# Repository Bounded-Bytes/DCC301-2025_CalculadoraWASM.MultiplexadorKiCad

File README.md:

# Repositório de Atividades Extras – AOC

### Autor: Gabriel Guilherme Figueiredo (2024005507)

Este repositório contém duas atividades extras para a disciplina de **AOC**:

1. **Calculadora WebAssembly**  
2. **Multiplexador 4x1 – KiCad e PCB**

---

## 1️⃣ Calculadora WebAssembly

- **Descrição:** Projeto de uma calculadora aritmética simples implementada em C, compilada para WebAssembly usando Emscripten, com interface HTML/JS.  
- **Ferramentas usadas:** C, Emscripten, HTML, JavaScript.  
- **Conteúdo da pasta `CalculadoraWASM`:**  
  - `index.html` → interface da calculadora  
  - `calculadora.c` → código C da calculadora  
  - `calculadora.js` e `calculadora.wasm` → arquivos gerados pelo Emscripten 

- **Como testar:**
  1. Fazer download da pasta `CalculadoraWASM`
  2. Rodar um servidor HTTP local (`python -m http.server 8000`)
  3. Abrir `http://localhost:8000` no navegador

---

## 2️⃣ Multiplexador 4x1 – KiCad

- **Descrição:** Projeto de um multiplexador 4x1, com esquemático completo e PCB pronta para fabricação.  
- **Ferramentas usadas:** KiCad.
- **Conteúdo da pasta `MultiplexadorKiCad`:**
  - `multiplexador.kicad_sch` → esquemático elétrico do circuito
  - `multiplexador.kicad_pcb` → layout da placa PCB
  - `imagem-esquematico.png`, `imagem-PCB-topo.png`, e `imagem-PCB-fundo.png` → imagens do diagrama e PCB do circuito

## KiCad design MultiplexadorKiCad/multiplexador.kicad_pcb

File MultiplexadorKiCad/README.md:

# Multiplexador 4x1

Este documento descreve o projeto de um **Multiplexador 4x1** implementado com **CIs da série 74LSxx**, incluindo o **esquemático elétrico** e a **estimativa de custo de fabricação da PCB** (Placa de Circuito Impresso).

---

## 1. Descrição do Circuito

O circuito implementa a lógica booleana de um **Multiplexador 4x1**, que seleciona uma entre quatro entradas de dados (`E0`, `E1`, `E2`, `E3`) e a encaminha para uma única saída (`OUT_final`), de acordo com a combinação de dois bits seletores (`S1`, `S0`).

### **Função lógica do circuito:** $$OUT_{\text{final}} = (E_0 \cdot \overline{S_1} \cdot \overline{S_0}) + (E_1 \cdot \overline{S_1} \cdot S_0) + (E_2 \cdot S_1 \cdot \overline{S_0}) + (E_3 \cdot S_1 \cdot S_0)$$

<p align="center">
  <br>
  <br>
  <em>Diagrama esquemático do multiplexador</em>
</p>

---

## 2. Lista de Componentes

| Componente | Quantidade | Custo Unitário Médio (R$) | Custo Total (R$) | Observações |
|:--|:--:|:--:|:--:|:--:|
| CI 74LS11 (Porta AND – 3 entradas) | 2 | 3,00 | 6,00 | 4 portas AND necessárias (3 do U1, 1 do U2) |
| CI 74LS04 (Inversor NOT) | 1 | 2,50 | 2,50 | Geração de $\overline{S_1}$ e $\overline{S_0}$ |
| CI 74LS32 (Porta OR – 2 entradas) | 1 | 2,50 | 2,50 | Três portas em cascata para OR de 4 entradas |
| Chave Nidec CAS-120A1 (SPDT Deslizante) | 6 | 2,00 | 12,00 | Chaves seletoras SPDT 3 pinos |
| Conector Pin Header (Conn_01x01) | 3 | 0,50 | 1,50 | Para VCC, GND e saída de dados ($OUT_{\text{final}}$).
| Resistor 330 Ω (1/4 W) | 1 | 0,50 | 0,50 | Limita corrente do LED |
| Mini LED (3 mm) | 1 | 1,00 | 1,00 | Indica visualmente a saída HIGH |
| **TOTAL** |  |  | **R$ 26,00** |

<p align="center">
  <br>
  
  <br>
  <em>Vista superior e inferior da Placa de Circuito Impresso</em>
</p>

---

## 3. Estimativa de Custo de Produção da PCB

A tabela abaixo mostra o custo médio de **componentes** e **fabricação** em protótipo de placa dupla face (aprox. 5 × 5 cm):

| Item | Quantidade | Custo Unitário (R$) | 
|:--|:--:|:--:|
| Custo dos componentes | 1 | 26,00 |
| Fabricação da placa (PCB – 5×5 cm, dupla face) | 1 | 18,00 – 36,00 |
| **Custo total estimado por placa** |  | **R$ 44,00 – 62,00** | 

**Detalhe:**  
O custo de fabricação (R$ 18 – 36 por unidade) foi obtido a partir da divisão do custo total de um lote de 5 placas (≈ R$ 90 – 180) em serviços de prototipagem de PCBs.

---

## 4. Arquivos do Projeto

- `multiplexador.kicad_sch` → esquemático elétrico do circuito
- `multiplexador.kicad_pcb` → layout da placa PCB
- `imagem-esquematico.png`, `imagem-PCB-topo.png`, e `imagem-PCB-fundo.png` → imagens do diagrama e PCB do circuito

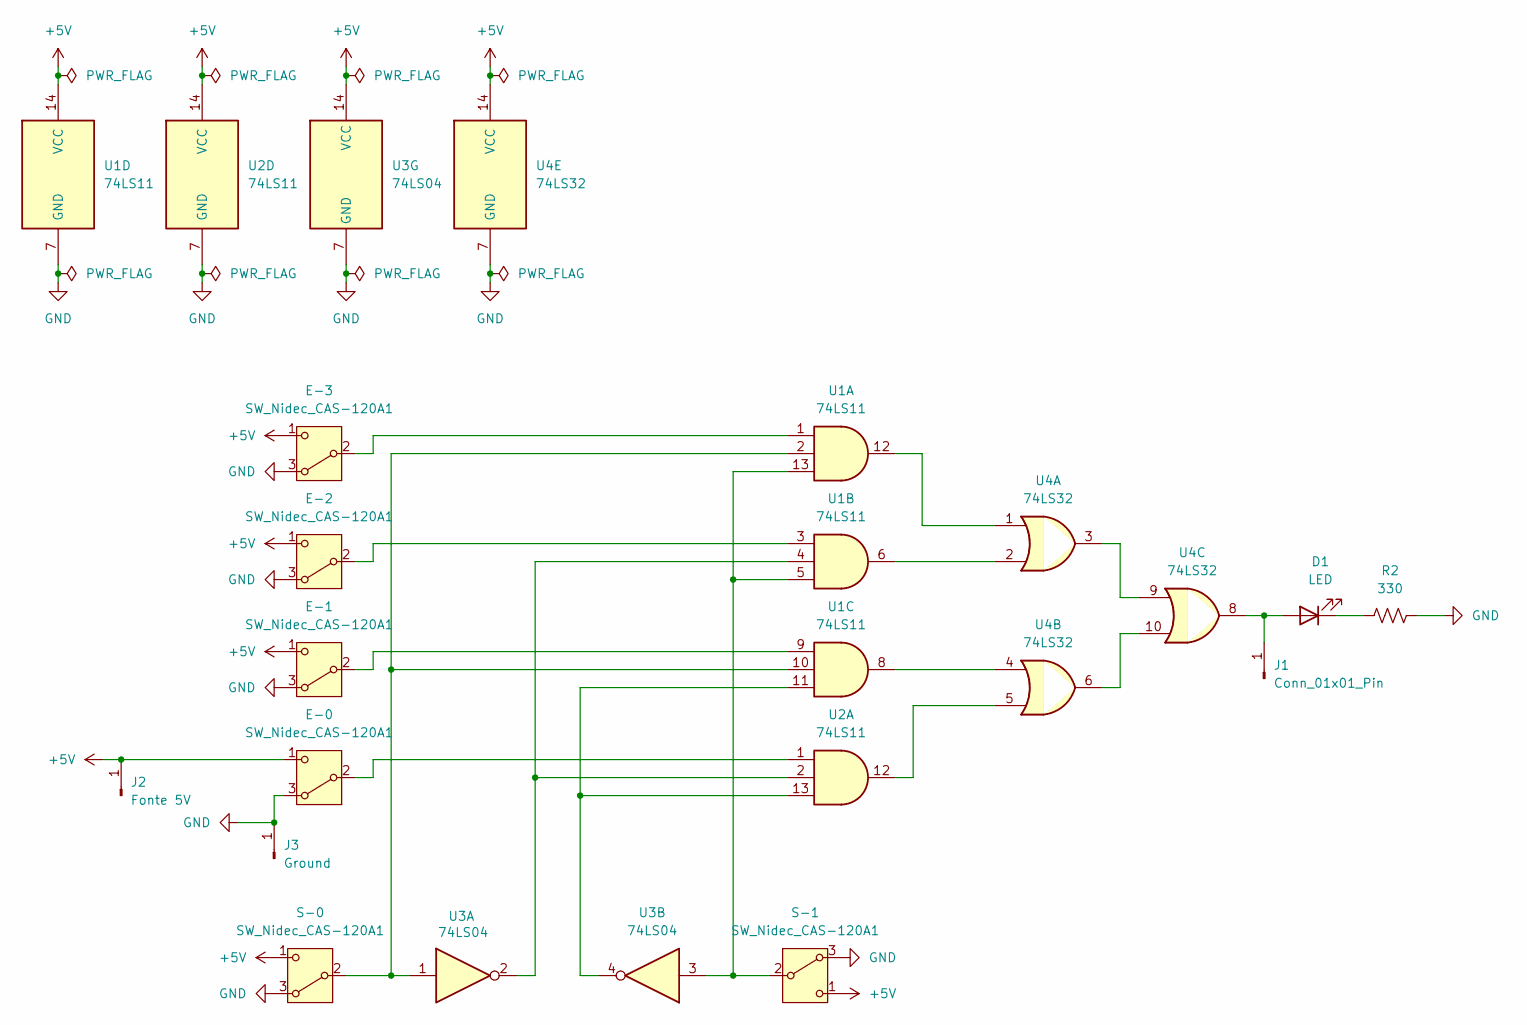
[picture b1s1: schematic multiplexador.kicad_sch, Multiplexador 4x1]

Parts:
D1: LED; LED_1206_3216Metric
E-0, E-1, E-2, E-3: SW_Nidec_CAS-120A1; Nidec_Copal_CAS-120A
J1: Conn_01x01_Pin; PinHeader_1x01_P2.54mm_Horizontal
J2: Fonte 5V; PinHeader_1x01_P2.54mm_Horizontal
J3: Ground; PinHeader_1x01_P2.54mm_Horizontal
R2: 330; R_1210_3225Metric
S-0, S-1: SW_Nidec_CAS-120A1; Nidec_Copal_CAS-120A
U1, U2: 74LS11; DIP-14_W7.62mm
U3: 74LS04; DIP-14_W7.62mm
U4: 74LS32; DIP-14_W7.62mm

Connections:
+5V: E-0.1 (C), E-1.1 (C), E-2.1 (C), E-3.1 (C), J2.1, S-0.1 (C), S-1.1 (C), U1.14 (VCC), U2.14 (VCC), U3.14 (VCC), U4.14 (VCC)
GND: E-0.3 (A), E-1.3 (A), E-2.3 (A), E-3.3 (A), J3.1, R2.1, S-0.3 (A), S-1.3 (A), U1.7 (GND), U2.7 (GND), U3.7 (GND), U4.7 (GND)
unnamed: D1.2 (A), J1.1, U4.8
unnamed: D1.1 (K), R2.2
unnamed: E-0.2 (B), U2.1
unnamed: E-1.2 (B), U1.9
unnamed: E-2.2 (B), U1.3
unnamed: E-3.2 (B), U1.1
unnamed: S-0.2 (B), U1.2, U1.10, U3.1
unnamed: S-1.2 (B), U1.5, U1.13, U3.3
unnamed: U1.4, U2.2, U3.2
unnamed: U1.6, U4.2
unnamed: U1.8, U4.4
unnamed: U1.11, U2.13, U3.4
unnamed: U1.12, U4.1
unnamed: U2.12, U4.5
unnamed: U4.3, U4.9
unnamed: U4.6, U4.10

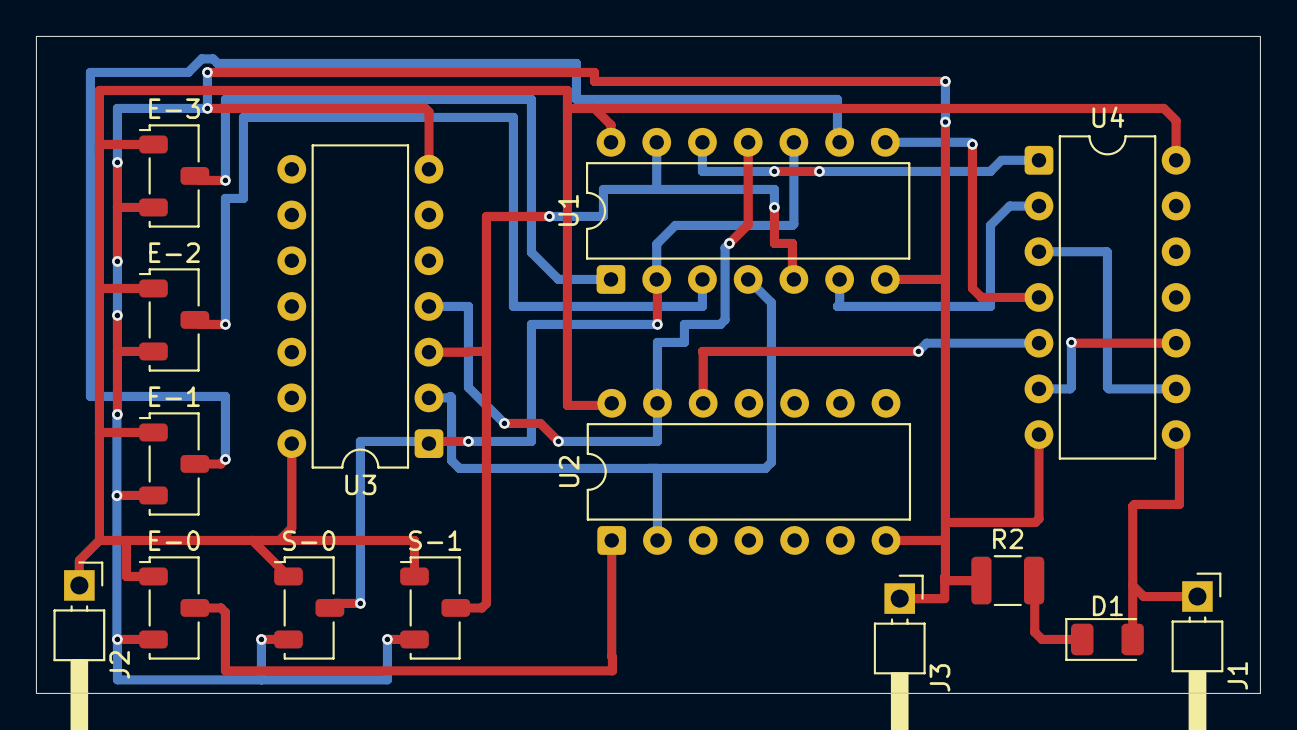
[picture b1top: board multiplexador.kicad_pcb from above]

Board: 2 copper layers, 68.0 x 36.5 mm, 15 parts (0 on the bottom side), 18 nets.
